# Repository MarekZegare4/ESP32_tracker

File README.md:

## Antenna tracker based on ESP32 microcontroller

This project focuses on the development of an antenna tracker with some ground station functionalities. Developed in platformio with Arduino framework. Based on [mLRS](https://github.com/olliw42/mLRS) project for MAVLink telemetry data.

### Contents of the repository
- `src` - source code of the project
- `schematic` - schematics and PCB design files
- `matlab_scripts` - magnetometer calibration routine

### Current features
- Tracking based on built-in GNSS receiver data and telemetry data from UAV
- 360° continuous rotation in vertical axis
- WiFi/BT/USB telemetry bridge
- Implemented magnetometer with calibration routine
### To be implemented
- GUI for configuration and monitoring on built-in display
- IMU pan and tilt stabilization
-
-
- More telemetry protocols

---

## Current PCB design

## Current mechanical design

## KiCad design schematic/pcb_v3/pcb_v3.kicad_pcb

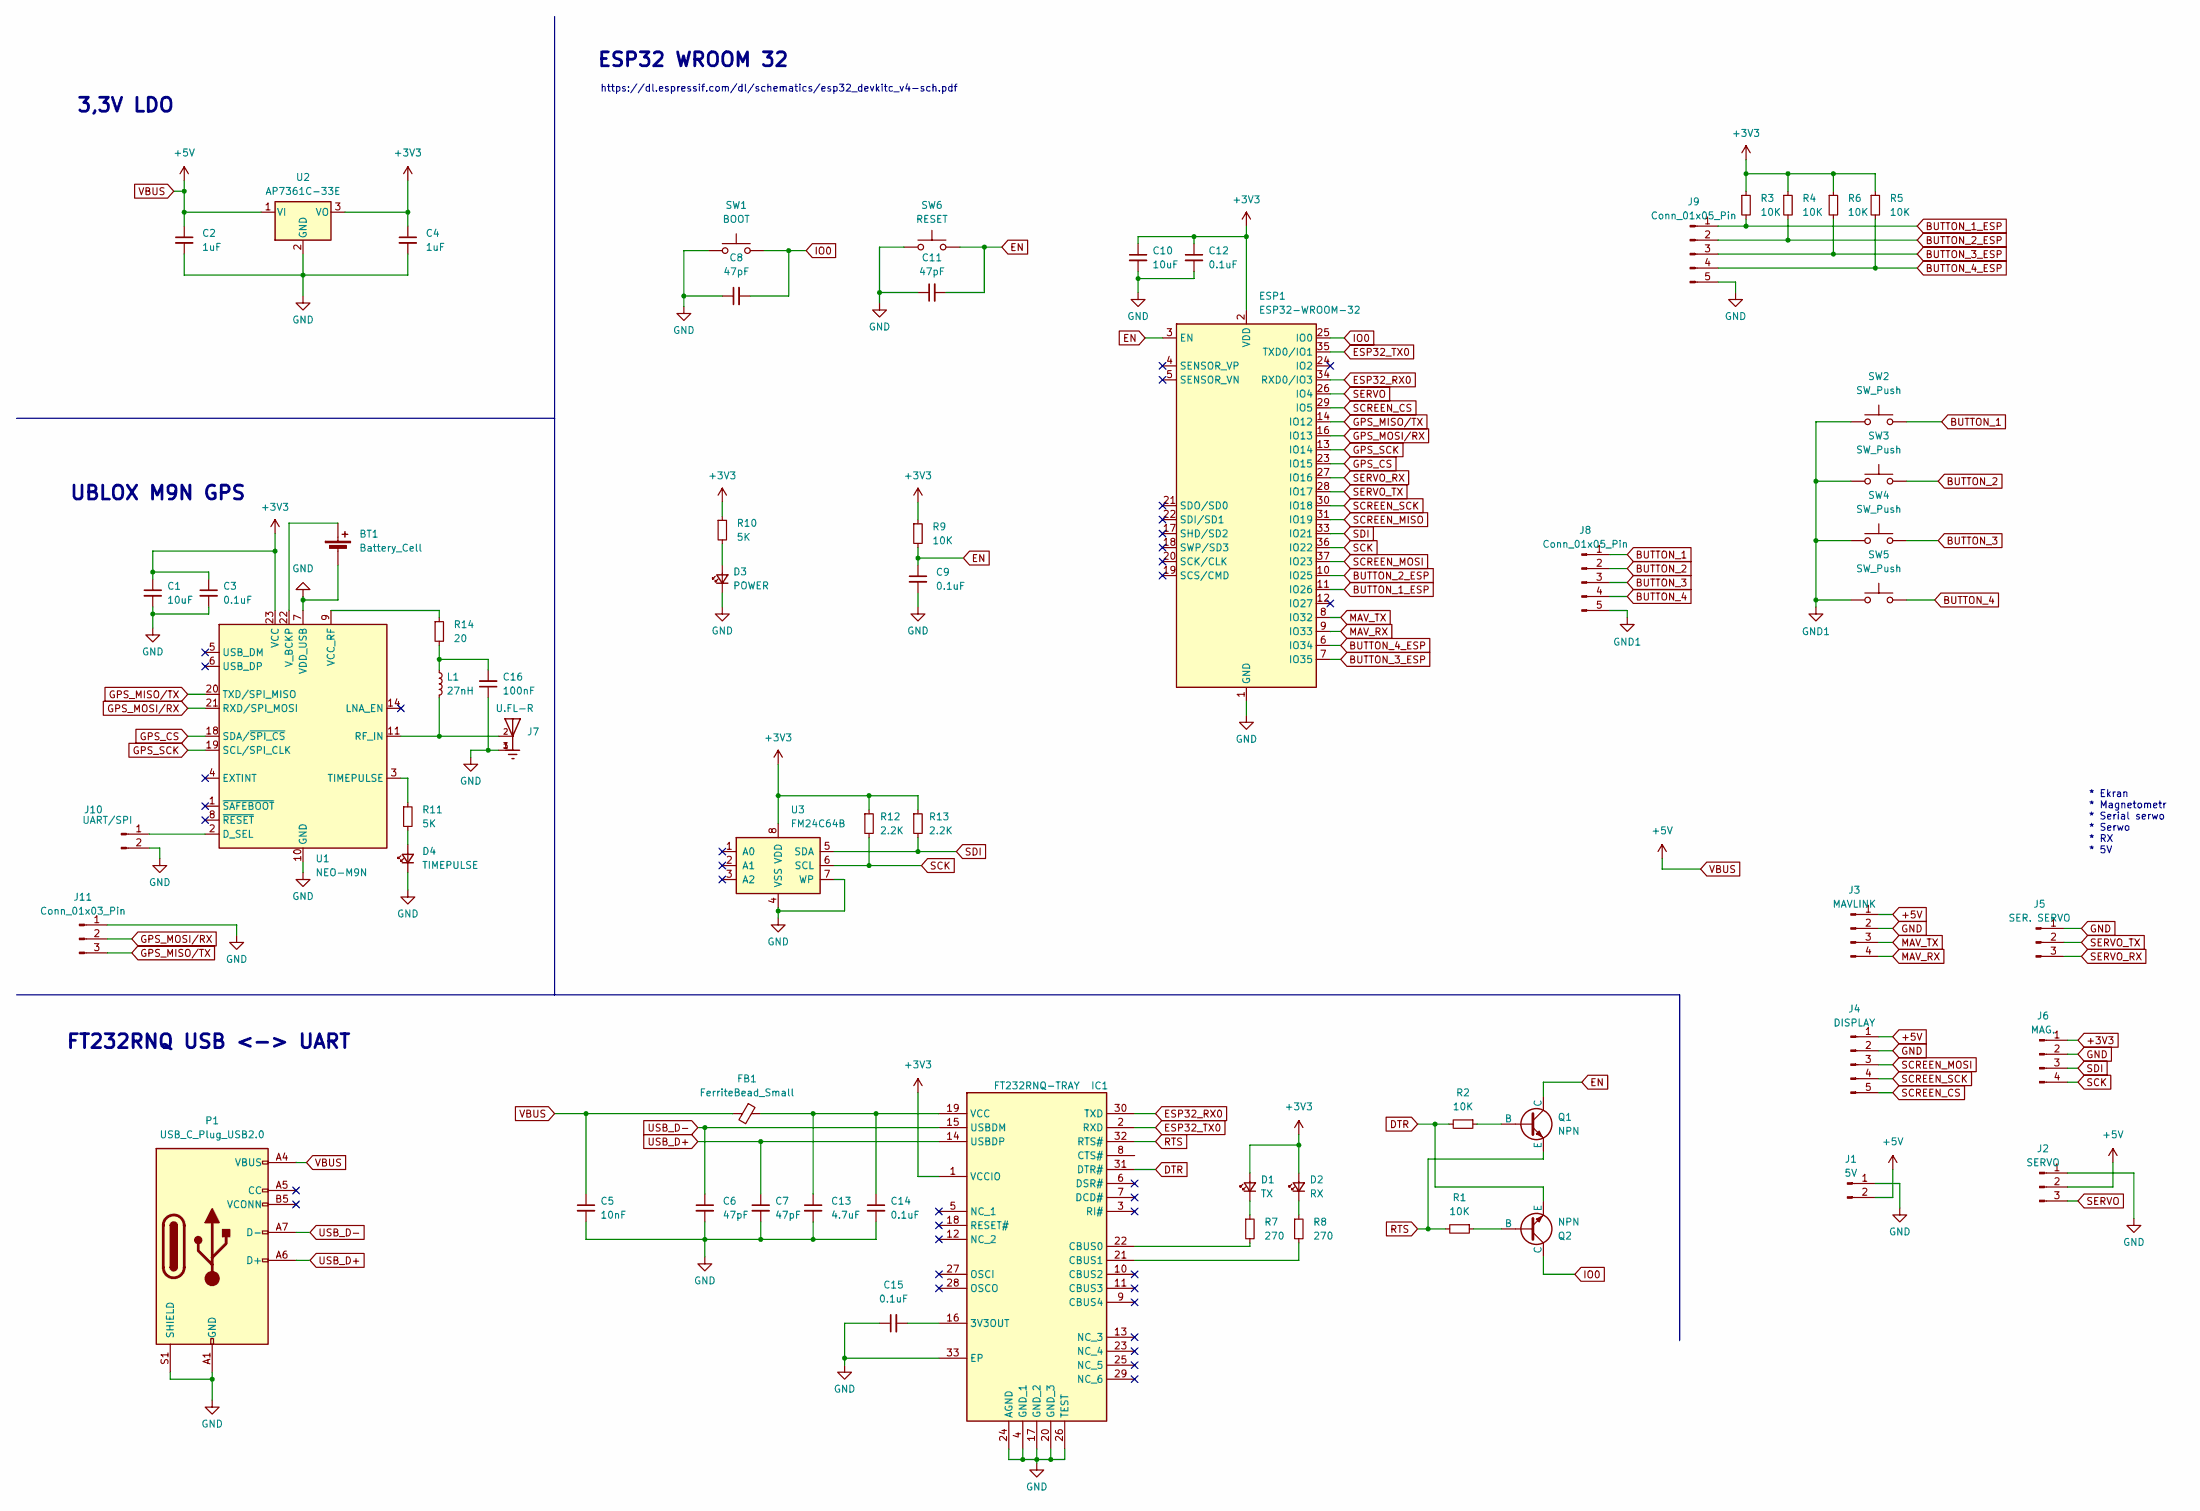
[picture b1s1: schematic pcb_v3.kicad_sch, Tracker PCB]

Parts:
BT1: Battery_Cell; BatteryHolder_Keystone_1060_1x2032
C1, C10: 10uF; C_0805_2012Metric
C2, C4: 1uF; C_0805_2012Metric
C3, C9, C12, C14, C15: 0.1uF; C_0805_2012Metric
C5: 10nF; C_0805_2012Metric
C6, C7, C8, C11: 47pF; C_0805_2012Metric
C13: 4.7uF; C_0805_2012Metric
C16: 100nF; C_0805_2012Metric
D1: TX; LED_0805_2012Metric
D2: RX; LED_0805_2012Metric
D3: POWER; LED_0805_2012Metric
D4: TIMEPULSE; LED_0805_2012Metric
ESP1: ESP32-WROOM-32; ESP32-WROOM-32UE
FB1: FerriteBead_Small; L_0805_2012Metric
IC1: FT232RNQ-TRAY; QFN50P500X500X90-33N-D; Mouser Part Number 895-FT232RNQ-TRAY
J1: 5V; PinHeader_1x02_P2.54mm_Vertical
J2: SERVO; PinHeader_1x03_P2.54mm_Vertical
J3: MAVLINK; JST_GH_BM04B-GHS-TBT_1x04-1MP_P1.25mm_Vertical
J4: DISPLAY; JST_GH_BM05B-GHS-TBT_1x05-1MP_P1.25mm_Vertical
J5: SER. SERVO; JST_GH_BM03B-GHS-TBT_1x03-1MP_P1.25mm_Vertical
J6: MAG.; JST_GH_BM04B-GHS-TBT_1x04-1MP_P1.25mm_Vertical
J7: U.FL-R; HRS_U.FL-R-SMT-1(10)
J8: Conn_01x05_Pin; PinHeader_1x05_P1.27mm_Vertical_SMD_Pin1Left
J9: Conn_01x05_Pin; JST_GH_BM05B-GHS-TBT_1x05-1MP_P1.25mm_Vertical
J10: UART/SPI; PinHeader_1x02_P2.54mm_Vertical
J11: Conn_01x03_Pin; PinHeader_1x03_P2.54mm_Vertical
L1: 27nH; L_0805_2012Metric
P1: USB_C_Plug_USB2.0; USB_C_Receptacle_HRO_TYPE-C-31-M-12
Q1, Q2: NPN; TSOT-23
R1, R2, R3, R4, R5, R6, R9: 10K; R_0805_2012Metric
R7, R8: 270; R_0805_2012Metric
R10, R11: 5K; R_0805_2012Metric
R12, R13: 2.2K; R_0805_2012Metric
R14: 20; R_0805_2012Metric
SW1: BOOT; SW_SPST_B3U-1000P
SW2, SW3, SW4, SW5: SW_Push; SW_SPST_B3SL-1002P
SW6: RESET; SW_SPST_B3U-1000P
U1: NEO-M9N; ublox_NEO
U2: AP7361C-33E; SOT-223-3_TabPin2
U3: FM24C64B; SON95P400X450X80-9N

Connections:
+3V3: C1.1, C3.1, C4.1, C10.1, C12.1, D1.2 (A), D2.2 (A), ESP1.2 (VDD), IC1.1 (VCCIO), J6.1, R3.1, R4.1, R5.1, R6.1, R9.1, R10.1, R12.1, R13.1, U1.23 (VCC), U2.3 (VO), U3.8 (VDD)
+5V: C2.1, C5.1, FB1.2, J1.2, J2.2, J3.1, J4.1, P1.A4 (VBUS), P1.A9 (VBUS), P1.B4 (VBUS), P1.B9 (VBUS), U2.1 (VI)
BUTTON_1: J8.1, SW2.2
BUTTON_1_ESP: ESP1.11 (IO26), J9.1, R3.2
BUTTON_2: J8.2, SW3.2
BUTTON_2_ESP: ESP1.10 (IO25), J9.2, R4.2
BUTTON_3: J8.3, SW4.2
BUTTON_3_ESP: ESP1.7 (IO35), J9.3, R6.2
BUTTON_4: J8.4, SW5.2
BUTTON_4_ESP: ESP1.6 (IO34), J9.4, R5.2
DTR: IC1.31 (DTR#), Q2.3 (E), R2.2
EN: C9.1, C11.2, ESP1.3 (EN), Q1.1 (C), R9.2, SW6.2
ESP32_RX0: ESP1.34 (RXD0/IO3), IC1.30 (TXD)
ESP32_TX0: ESP1.35 (TXD0/IO1), IC1.2 (RXD)
GND: BT1.2 (-), C1.2, C2.2, C3.2, C4.2, C5.2, C6.2, C7.2, C8.1, C9.2, C10.2, C11.1, C12.2, C13.2, C14.2, C15.1, C16.1, D3.1 (K), D4.1 (K), ESP1.1 (GND), ESP1.15 (GND), ESP1.38 (GND), ESP1.39 (GND), IC1.4 (GND_1), IC1.17 (GND_2), IC1.20 (GND_3), IC1.24 (AGND), IC1.26 (TEST), IC1.33 (EP), J1.1, J2.1, J3.2, J4.2, J5.1, J6.2, J7.1, J7.3, J9.5, J10.2, J11.1, P1.A1 (GND), P1.A12 (GND), P1.B1 (GND), P1.B12 (GND), P1.S1 (SHIELD), SW1.1, SW6.1, U1.7 (VDD_USB), U1.10 (GND), U1.12 (GND), U1.13 (GND), U1.24 (GND), U2.2 (GND), U3.4 (VSS), U3.7 (WP)
GND1: J8.5, SW2.1, SW3.1, SW4.1, SW5.1
GPS_CS: ESP1.23 (IO15), U1.18 (SDA/~SPI_CS)
GPS_MISO/TX: ESP1.14 (IO12), J11.3, U1.20 (TXD/SPI_MISO)
GPS_MOSI/RX: ESP1.16 (IO13), J11.2, U1.21 (RXD/SPI_MOSI)
GPS_SCK: ESP1.13 (IO14), U1.19 (SCL/SPI_CLK)
IO0: C8.2, ESP1.25 (IO0), Q2.1 (C), SW1.2
MAV_RX: ESP1.9 (IO33), J3.4
MAV_TX: ESP1.8 (IO32), J3.3
unnamed: BT1.1 (+), U1.22 (V_BCKP)
unnamed: C16.2, L1.1, R14.2
unnamed: D1.1 (K), R7.1
unnamed: D2.1 (K), R8.1
unnamed: D3.2 (A), R10.2
unnamed: D4.2 (A), R11.2
unnamed: C15.2, IC1.16 (3V3OUT)
unnamed: IC1.22 (CBUS0), R7.2
unnamed: IC1.21 (CBUS1), R8.2
unnamed: C13.1, C14.1, FB1.1, IC1.19 (VCC)
unnamed: J10.1, U1.2 (D_SEL)
unnamed: Q1.2 (B), R2.1
unnamed: Q2.2 (B), R1.1
unnamed: J7.2, L1.2, U1.11 (RF_IN)
unnamed: R11.1, U1.3 (TIMEPULSE)
unnamed: R14.1, U1.9 (VCC_RF)
RTS: IC1.32 (RTS#), Q1.3 (E), R1.2
SCK: ESP1.36 (IO22), J6.4, R12.2, U3.6 (SCL)
SCREEN_CS: ESP1.29 (IO5), J4.5
SCREEN_MISO: ESP1.31 (IO19)
SCREEN_MOSI: ESP1.37 (IO23), J4.3
SCREEN_SCK: ESP1.30 (IO18), J4.4
SDI: ESP1.33 (IO21), J6.3, R13.2, U3.5 (SDA)
SERVO: ESP1.26 (IO4), J2.3
SERVO_RX: ESP1.27 (IO16), J5.3
SERVO_TX: ESP1.28 (IO17), J5.2
USB_D+: C7.1, IC1.14 (USBDP), P1.A6 (D+)
USB_D-: C6.1, IC1.15 (USBDM), P1.A7 (D-)

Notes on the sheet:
* Ekran * Magnetometr * Serial serwo * Serwo * RX * 5V
FT232RNQ USB <-> UART
https://dl.espressif.com/dl/schematics/esp32_devkitc_v4-sch.pdf
3,3V LDO
ESP32 WROOM 32
UBLOX M9N GPS

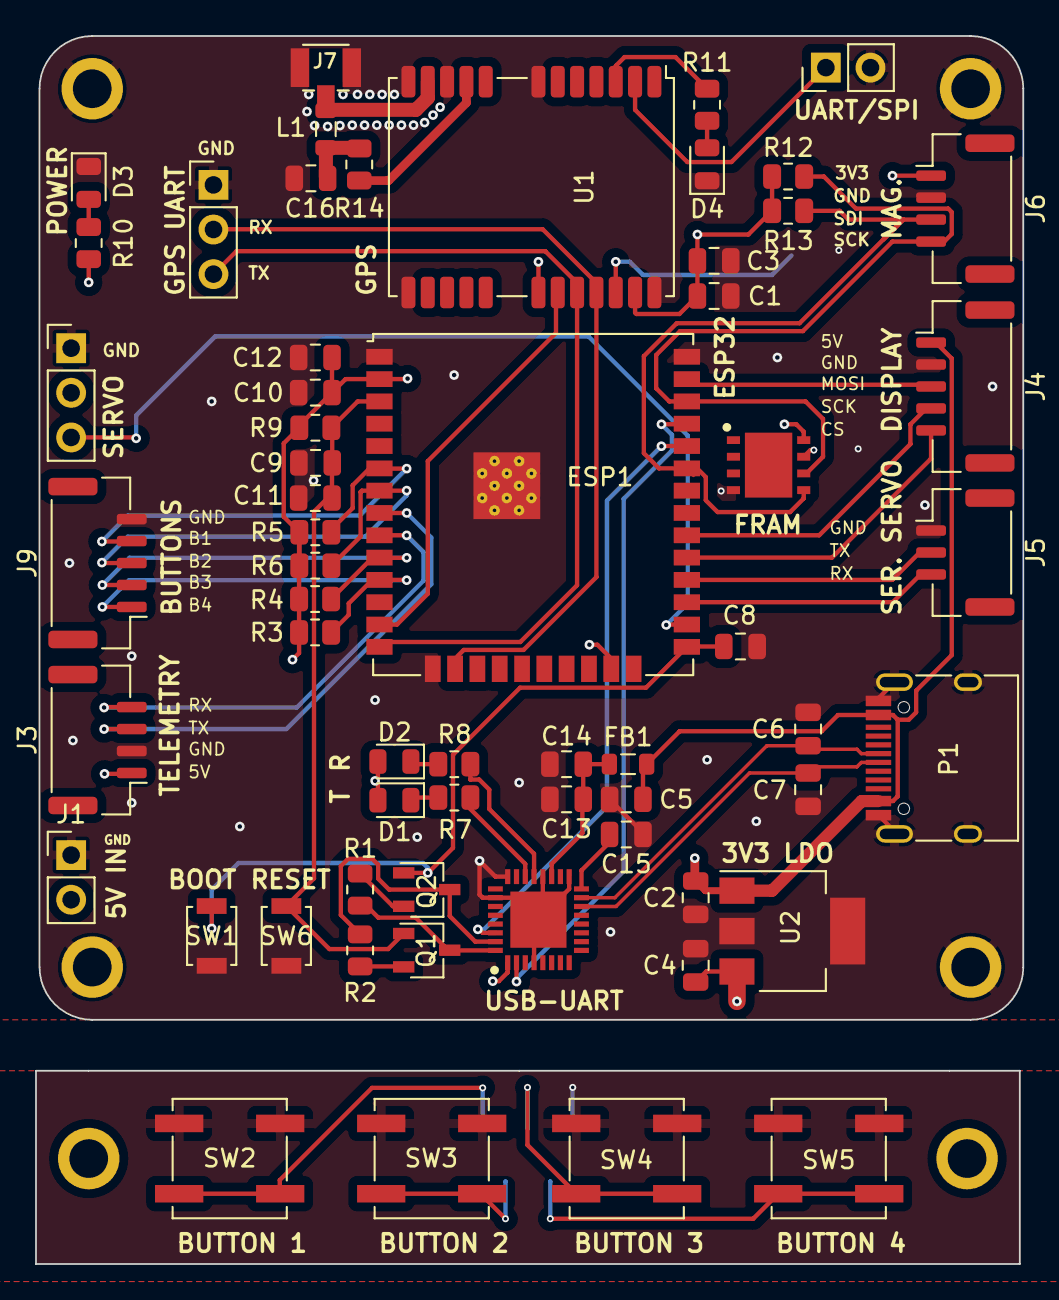
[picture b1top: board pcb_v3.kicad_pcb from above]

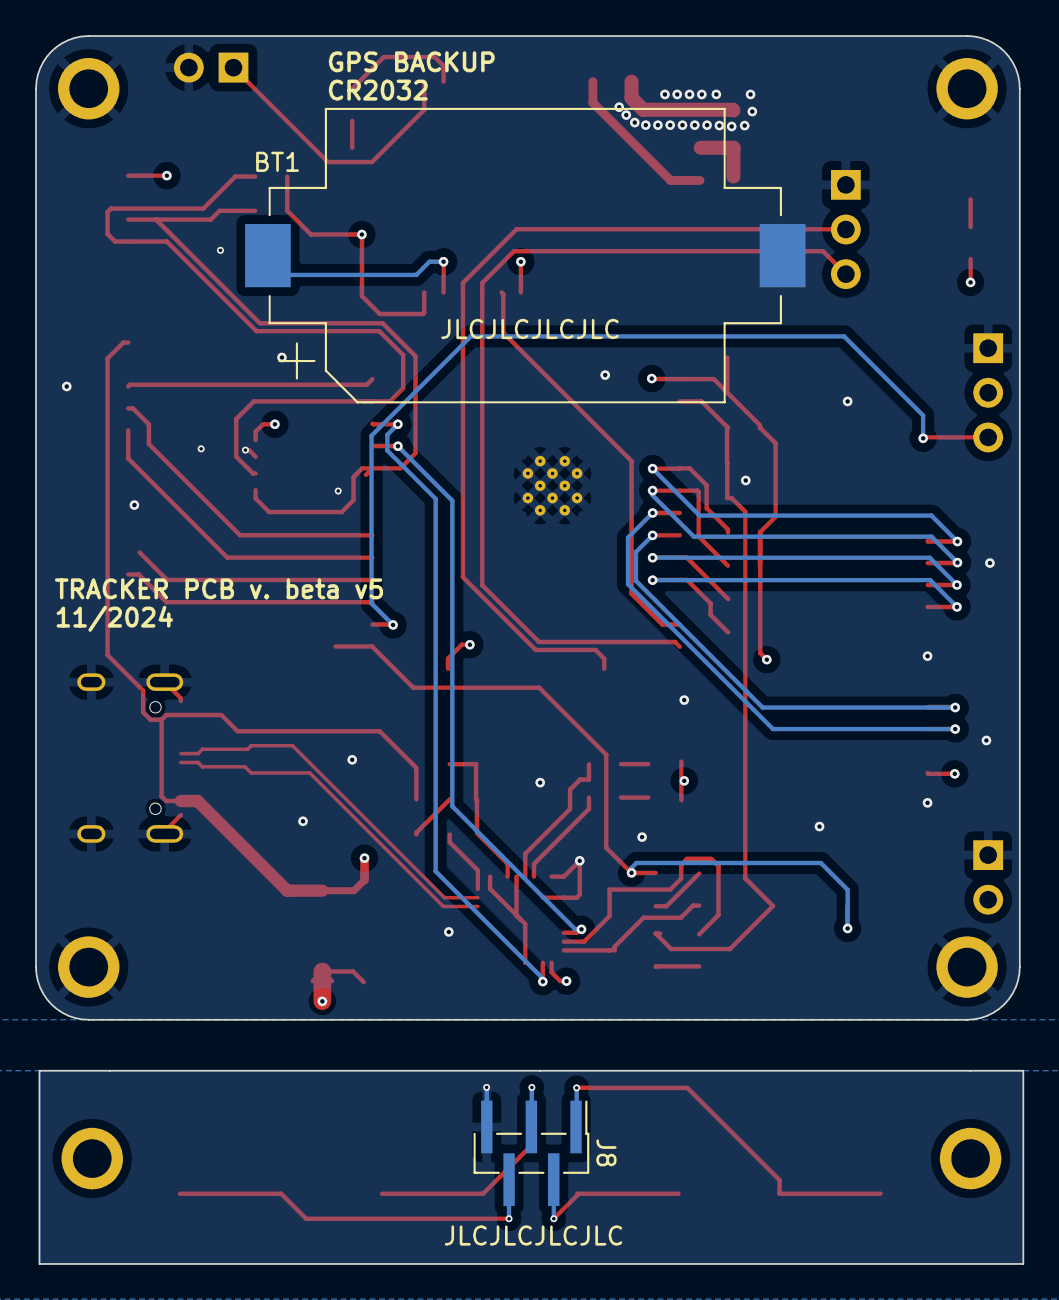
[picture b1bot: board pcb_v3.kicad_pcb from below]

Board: 4 copper layers, 56.2 x 69.9 mm, 62 parts (2 on the bottom side), 50 nets.

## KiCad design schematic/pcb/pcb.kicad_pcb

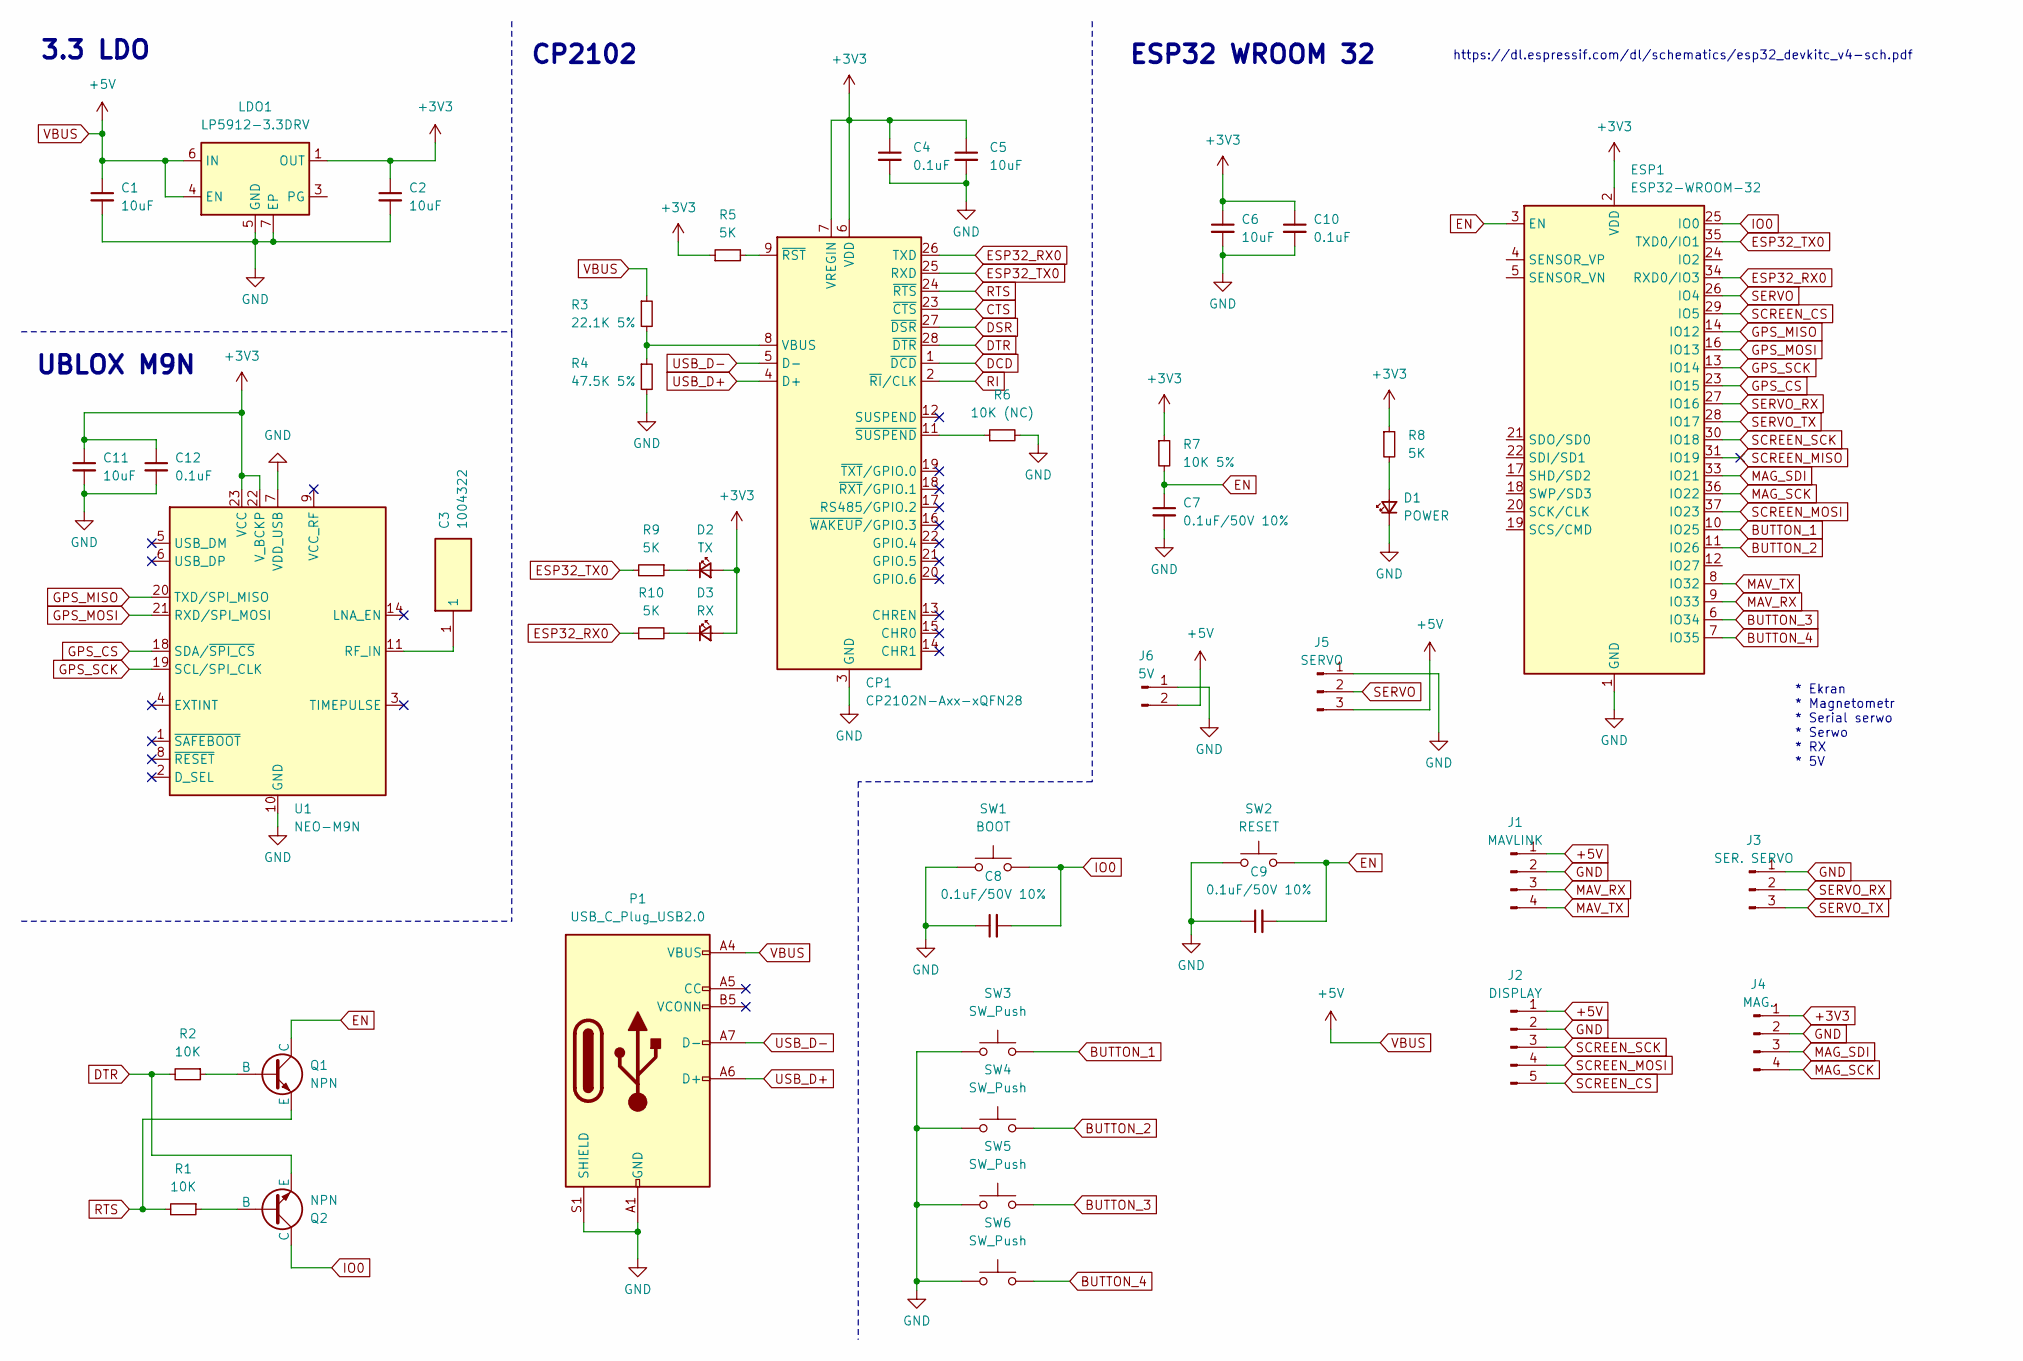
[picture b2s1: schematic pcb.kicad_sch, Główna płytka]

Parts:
C1, C2, C5, C6, C11: 10uF; C_0805_2012Metric
C3: 1004322; GPS_ANTENNA; Mouser Part Number 581-1004322
C4, C10, C12: 0.1uF; C_0805_2012Metric
C7, C8, C9: 0.1uF/50V 10%; C_0805_2012Metric
CP1: CP2102N-Axx-xQFN28; QFN-28-1EP_5x5mm_P0.5mm_EP3.35x3.35mm
D1: POWER; LED_0805_2012Metric
D2: TX; LED_0805_2012Metric
D3: RX; LED_0805_2012Metric
ESP1: ESP32-WROOM-32
J1: MAVLINK; JST_GH_BM04B-GHS-TBT_1x04-1MP_P1.25mm_Vertical
J2: DISPLAY; JST_GH_BM05B-GHS-TBT_1x05-1MP_P1.25mm_Vertical
J3: SER. SERVO; JST_GH_BM03B-GHS-TBT_1x03-1MP_P1.25mm_Vertical
J4: MAG.; JST_GH_BM04B-GHS-TBT_1x04-1MP_P1.25mm_Vertical
J5: SERVO; PinHeader_1x03_P2.54mm_Vertical
J6: 5V; PinHeader_1x02_P2.54mm_Vertical
LDO1: LP5912-3.3DRV; WSON-6-1EP_2x2mm_P0.65mm_EP1x1.6mm_ThermalVias
P1: USB_C_Plug_USB2.0; USB_C_Receptacle_HRO_TYPE-C-31-M-12
Q1, Q2: NPN; TSOT-23
R1, R2: 10K; R_0805_2012Metric
R3: 22.1K 5%; R_0805_2012Metric
R4: 47.5K 5%; R_0805_2012Metric
R5, R8, R9, R10: 5K; R_0805_2012Metric
R6: 10K (NC); R_0805_2012Metric
R7: 10K 5%; R_0805_2012Metric
SW1: BOOT; SW_SPST_B3U-1000P
SW2: RESET; SW_SPST_B3U-1000P
SW3, SW4, SW5, SW6: SW_Push; SW_SPST_B3SL-1002P
U1: NEO-M9N; ublox_NEO

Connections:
+3V3: C2.1, C4.1, C5.1, C6.1, C10.1, C11.1, C12.1, CP1.6 (VDD), CP1.7 (VREGIN), D2.2 (A), D3.2 (A), ESP1.2 (VDD), J4.1, LDO1.1 (OUT), R5.1, R7.1, R8.1, U1.22 (V_BCKP), U1.23 (VCC)
+5V: C1.1, J1.1, J2.1, J5.3, J6.2, LDO1.4 (EN), LDO1.6 (IN), P1.A4 (VBUS), P1.A9 (VBUS), P1.B4 (VBUS), P1.B9 (VBUS), R3.1
BUTTON_1: ESP1.10 (IO25), SW3.2
BUTTON_2: ESP1.11 (IO26), SW4.2
BUTTON_3: ESP1.6 (IO34), SW5.2
BUTTON_4: ESP1.7 (IO35), SW6.2
CTS: CP1.23 (~CTS)
DCD: CP1.1 (~DCD)
DSR: CP1.27 (~DSR)
DTR: CP1.28 (~DTR), Q2.3 (E), R2.2
EN: C7.1, C9.2, ESP1.3 (EN), Q1.1 (C), R7.2, SW2.2
ESP32_RX0: CP1.26 (TXD), ESP1.34 (RXD0/IO3), R10.1
ESP32_TX0: CP1.25 (RXD), ESP1.35 (TXD0/IO1), R9.2
GND: C1.2, C2.2, C4.2, C5.2, C6.2, C7.2, C8.1, C9.1, C10.2, C11.2, C12.2, CP1.3 (GND), CP1.29 (GND), D1.1 (K), ESP1.1 (GND), ESP1.15 (GND), ESP1.38 (GND), ESP1.39 (GND), J1.2, J2.2, J3.1, J4.2, J5.1, J6.1, LDO1.5 (GND), LDO1.7 (EP), P1.A1 (GND), P1.A12 (GND), P1.B1 (GND), P1.B12 (GND), P1.S1 (SHIELD), R4.2, R6.2, SW1.1, SW2.1, SW3.1, SW4.1, SW5.1, SW6.1, U1.7 (VDD_USB), U1.10 (GND), U1.12 (GND), U1.13 (GND), U1.24 (GND)
GPS_CS: ESP1.23 (IO15), U1.18 (SDA/~SPI_CS)
GPS_MISO: ESP1.14 (IO12), U1.20 (TXD/SPI_MISO)
GPS_MOSI: ESP1.16 (IO13), U1.21 (RXD/SPI_MOSI)
GPS_SCK: ESP1.13 (IO14), U1.19 (SCL/SPI_CLK)
IO0: C8.2, ESP1.25 (IO0), Q2.1 (C), SW1.2
MAG_SCK: ESP1.36 (IO22), J4.4
MAG_SDI: ESP1.33 (IO21), J4.3
MAV_RX: ESP1.9 (IO33), J1.3
MAV_TX: ESP1.8 (IO32), J1.4
unnamed: CP1.8 (VBUS), R3.2, R4.1
unnamed: CP1.9 (~RST), R5.2
unnamed: CP1.11 (~SUSPEND), R6.1
unnamed: D1.2 (A), R8.2
unnamed: D2.1 (K), R9.1
unnamed: D3.1 (K), R10.2
unnamed: Q1.2 (B), R2.1
unnamed: Q2.2 (B), R1.1
unnamed: C3.1, U1.11 (RF_IN)
RI: CP1.2 (~RI/CLK)
RTS: CP1.24 (~RTS), Q1.3 (E), R1.2
SCREEN_CS: ESP1.29 (IO5), J2.5
SCREEN_MISO: ESP1.31 (IO19)
SCREEN_MOSI: ESP1.37 (IO23), J2.4
SCREEN_SCK: ESP1.30 (IO18), J2.3
SERVO: ESP1.26 (IO4), J5.2
SERVO_RX: ESP1.27 (IO16), J3.2
SERVO_TX: ESP1.28 (IO17), J3.3
USB_D+: CP1.4 (D+), P1.A6 (D+)
USB_D-: CP1.5 (D-), P1.A7 (D-)

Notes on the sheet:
CP2102
* Ekran * Magnetometr * Serial serwo * Serwo * RX * 5V
https://dl.espressif.com/dl/schematics/esp32_devkitc_v4-sch.pdf
UBLOX M9N
ESP32 WROOM 32
3.3 LDO

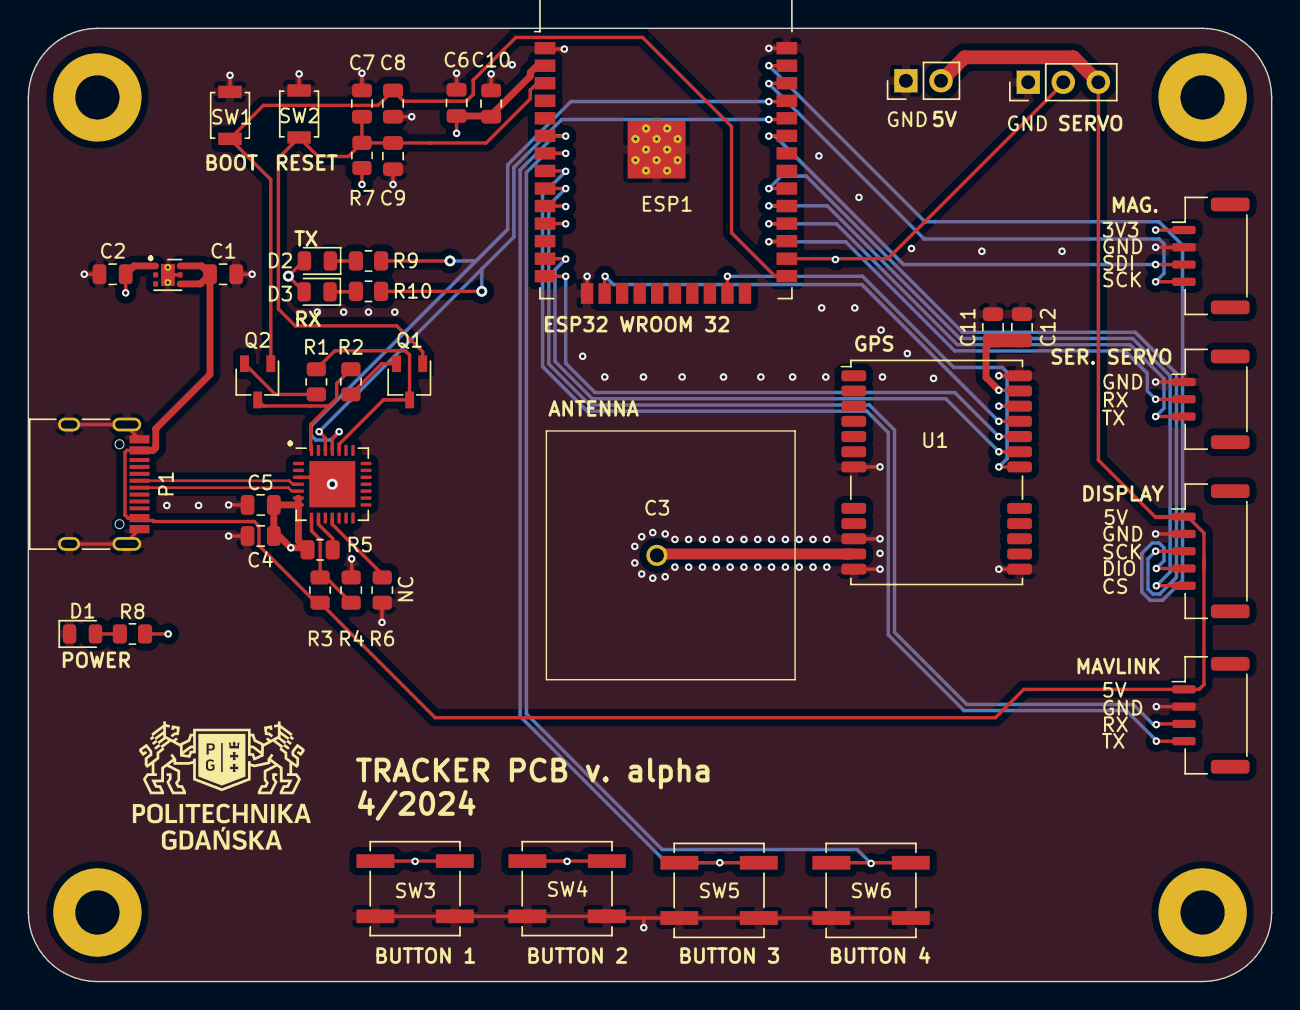
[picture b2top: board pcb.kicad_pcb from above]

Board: 4 copper layers, 90.0 x 69.0 mm, 44 parts (0 on the bottom side), 38 nets.

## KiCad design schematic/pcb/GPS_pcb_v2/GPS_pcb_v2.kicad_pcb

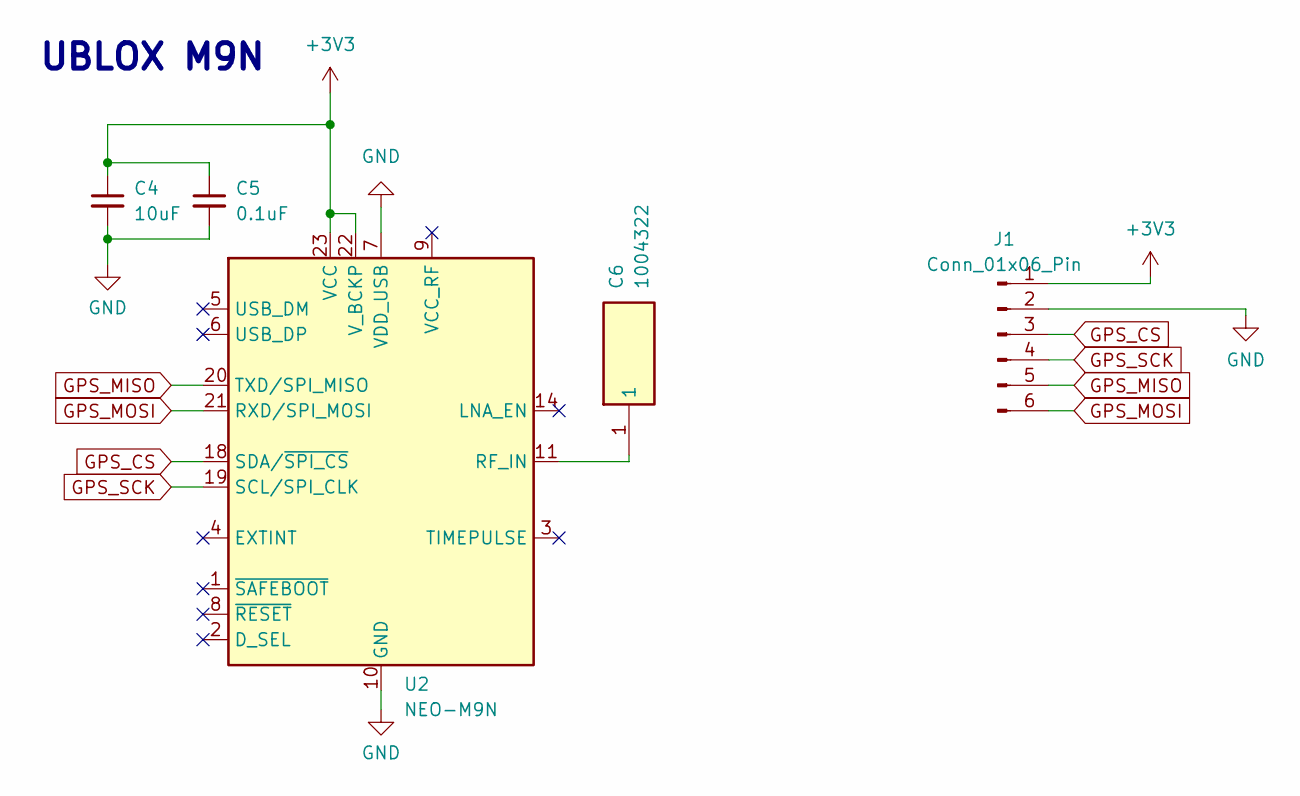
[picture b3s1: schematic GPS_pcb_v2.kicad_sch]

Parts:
C4: 10uF; C_0805_2012Metric
C5: 0.1uF; C_0805_2012Metric
C6: 1004322; GPS_ANTENNA; Mouser Part Number 581-1004322
J1: Conn_01x06_Pin; JST_GH_BM06B-GHS-TBT_1x06-1MP_P1.25mm_Vertical
U2: NEO-M9N; ublox_NEO

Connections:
+3V3: C4.1, C5.1, J1.1, U2.22 (V_BCKP), U2.23 (VCC)
GND: C4.2, C5.2, J1.2, U2.7 (VDD_USB), U2.10 (GND), U2.12 (GND), U2.13 (GND), U2.24 (GND)
GPS_CS: J1.3, U2.18 (SDA/~SPI_CS)
GPS_MISO: J1.5, U2.20 (TXD/SPI_MISO)
GPS_MOSI: J1.6, U2.21 (RXD/SPI_MOSI)
GPS_SCK: J1.4, U2.19 (SCL/SPI_CLK)
unnamed: C6.1, U2.11 (RF_IN)

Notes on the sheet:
UBLOX M9N

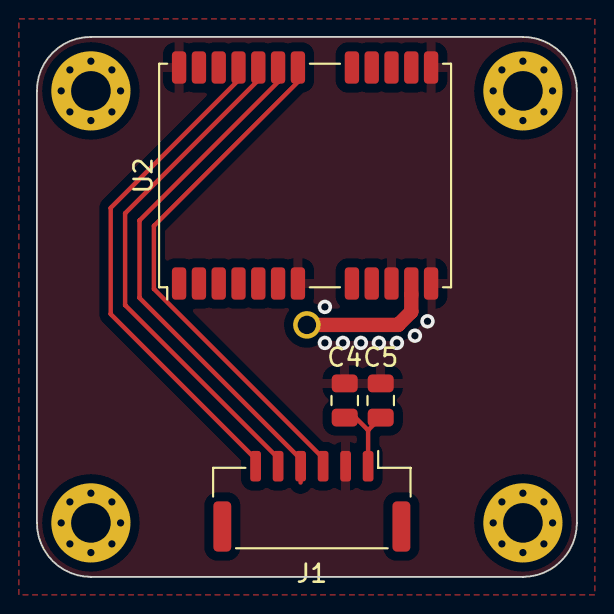
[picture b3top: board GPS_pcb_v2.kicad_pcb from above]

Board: 2 copper layers, 30.0 x 30.0 mm, 5 parts (1 on the bottom side), 7 nets.

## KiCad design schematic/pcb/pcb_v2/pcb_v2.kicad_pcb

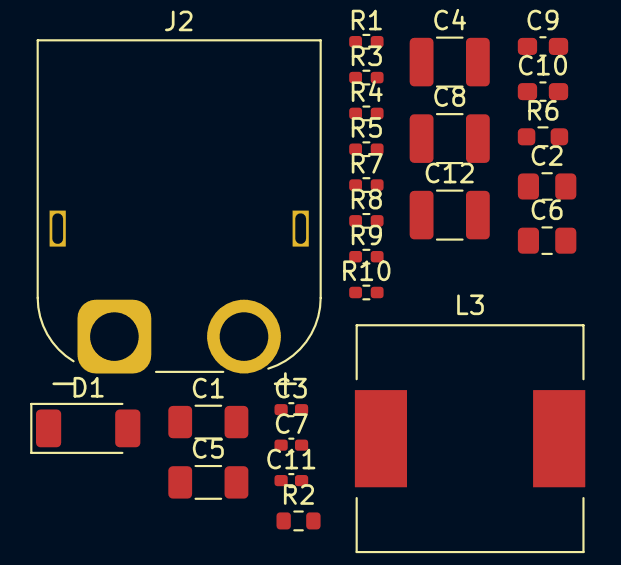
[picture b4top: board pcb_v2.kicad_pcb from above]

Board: 2 copper layers, 25 parts (0 on the bottom side), 10 nets, no tracks yet.

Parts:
C1, C5: 4.7uF; C_1206_3216Metric_Pad1.33x1.80mm_HandSolder
C2, C6: 100nF; C_0805_2012Metric_Pad1.18x1.45mm_HandSolder
C3, C7, C11: 100nF; C_0402_1005Metric_Pad0.74x0.62mm_HandSolder
C4: 100uF; C_1210_3225Metric_Pad1.33x2.70mm_HandSolder
C8, C12: 47uF; C_1210_3225Metric_Pad1.33x2.70mm_HandSolder
C9: 4.7uF; C_0603_1608Metric_Pad1.08x0.95mm_HandSolder
C10: 100nF; C_0603_1608Metric_Pad1.08x0.95mm_HandSolder
D1: D_Small; D_SOD-128
J2: XT60PW-M; AMASS_XT60PW-M_1x02_P7.20mm_Horizontal
L3: 15uH; L_12x12mm_H8mm
R1: 18.7k; R_0402_1005Metric_Pad0.72x0.64mm_HandSolder
R2: 100k; R_0603_1608Metric
R3, R7: 100k; R_0402_1005Metric_Pad0.72x0.64mm_HandSolder
R4: 32k; R_0402_1005Metric_Pad0.72x0.64mm_HandSolder
R5: 13.3k; R_0402_1005Metric_Pad0.72x0.64mm_HandSolder
R6: 100k; R_0603_1608Metric_Pad0.98x0.95mm_HandSolder
R8: 19.1k; R_0402_1005Metric_Pad0.72x0.64mm_HandSolder
R9: 422k; R_0402_1005Metric_Pad0.72x0.64mm_HandSolder
R10: 22.1k; R_0402_1005Metric_Pad0.72x0.64mm_HandSolder

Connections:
3V3_FB: R3.2, R4.1
5V_FB: R7.2, R8.1
12V_SW: C11.2, L3.1
+3V3: C4.1, R2.2, R3.1
+5V: C8.1, R6.2, R7.1
+12V: C12.2, L3.2, R9.1
+24V: C1.1, C2.1, C5.1, C6.1, C9.1, C10.1, D1.1 (K)
/FB_12V: R9.2, R10.1
GND: C1.2, C2.2, C4.2, C5.2, C6.2, C8.2, C9.2, C10.2, C12.1, J2.1, R1.2, R4.2, R5.2, R8.2, R10.2
unnamed: D1.2 (A), J2.2

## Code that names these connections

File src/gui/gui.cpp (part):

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#define WHITE 1
#define FREQ_2MHZ 2000000
#define FPS 30
#define BUTTON_1_PIN 26
#define BUTTON_2_PIN 25
#define BUTTON_3_PIN 35
#define BUTTON_4_PIN 34

// Useful links:
// https://javl.github.io/image2cpp/
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 */
void guiInitialize()
{
	pinMode(BUTTON_1_PIN, INPUT);
	pinMode(BUTTON_2_PIN, INPUT);
	pinMode(BUTTON_3_PIN, INPUT);
	pinMode(BUTTON_4_PIN, INPUT);
	attachInterrupt(digitalPinToInterrupt(BUTTON_1_PIN), button_1ISR, FALLING);
	attachInterrupt(digitalPinToInterrupt(BUTTON_2_PIN), button_2ISR, FALLING);
	attachInterrupt(digitalPinToInterrupt(BUTTON_3_PIN), button_3ISR, FALLING);
	attachInterrupt(digitalPinToInterrupt(BUTTON_4_PIN), button_4ISR, FALLING);
	display.begin();
	display.clearDisplay();
}
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
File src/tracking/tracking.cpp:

#include <Arduino.h>
#include <SCServo.h>
#include <Wire.h>
#include <SPI.h>
#include <Adafruit_LIS3MDL.h>
#include <Adafruit_LSM6DS3TRC.h>
#include <Adafruit_Sensor.h>
#include <ESP32Servo.h>
#include <SparkFun_u-blox_GNSS_v3.h>
#include <WMM_Tinier.h>
#include <SensorFusion.h>
#include "gui/gui.h"
#include "mavlink/mav.h"
#include "tracking.h"
#include "tracking/geoTransform/geoTransform.h"
#include "imu_calibration/imu_calibration.h"
#include "kalman_filter/kalman.h"
// https://www.waveshare.com/wiki/ST3020_Servo#Overview

#define SERVO_RX 16
#define SERVO_TX 17
#define SERVO_TILT_PIN 4
#define myCS 15              // Define the GPIO pin number for the SPI Chip Select. Change this if required
#define myClockSpeed 1000000 // Define what SPI clock speed to use. Change this if required

Servo servo;
// Serial Servo ST3020
SMS_STS st;
// Magnetometer
Adafruit_LIS3MDL lis3mdl;
// Accelerometer and Gyroscope
Adafruit_LSM6DS3TRC lsm6ds3trc;
// GNSS
SFE_UBLOX_GNSS_SPI myGNSS; // SFE_UBLOX_GNSS_SPI uses SPI. For I2C or Serial, see Example1 and Example2
SPIClass spiPort(HSPI);

WMM_Tinier declination;
TrackerDataGPS gpsData;
AngleValues sDistAziElev;
float sCompassDegree;
Wgs84Coord uavCoord;
Wgs84Coord trackerCoord;

// Sensor fusion
SF fusion;
float mx, my, mz, ax, ay, az, gx, gy, gz;
float pitch, roll, yaw;
float deltat;
float heading;

CalibratedIMUData mag_data;
CalibratedIMUData accel_data;

bool ready_to_track = false;

/*
@brief Corrects the angle to work in the current configuration
@param angle: wanted angle
*/
int servoAngle(int angle)
{
  return map(angle, 0, 90, 14, 170);
}

void trackingInitialize()
{
  Serial1.begin(1000000, SERIAL_8N1, SERVO_RX, SERVO_TX);
  declination.begin();
  st.pSerial = &Serial1;
  // st.CalibrationOfs(1);
  st.WritePosEx(1, 0, 1000, 100);
  ESP32PWM::allocateTimer(0);
  servo.setPeriodHertz(50);                 // Standard 50hz servo
  servo.attach(SERVO_TILT_PIN, 1000, 2000); // attaches the servo on pin 4 to the servo object
  servo.write(servoAngle(0));
  lis3mdl.begin_I2C();
  lis3mdl.setRange(LIS3MDL_RANGE_4_GAUSS);
  lis3mdl.setDataRate(LIS3MDL_DATARATE_80_HZ);
  lis3mdl.setPerformanceMode(LIS3MDL_HIGHMODE);
  lis3mdl.setOperationMode(LIS3MDL_CONTINUOUSMODE);
  lsm6ds3trc.begin_I2C();
  lsm6ds3trc.setGyroDataRate(LSM6DS_RATE_104_HZ);
  lsm6ds3trc.setAccelDataRate(LSM6DS_RATE_104_HZ);
  while (myGNSS.begin(spiPort, myCS, myClockSpeed) == false) // Connect to the u-blox module using the port, chip select pin and speed defined above
  {
    delay(1000);
  }
  myGNSS.setSPIOutput(COM_TYPE_UBX); // Set the SPI port to output UBX only (turn off NMEA noise)
  myGNSS.setNavigationFrequency(5);  // Set the update rate to 5Hz
}

void sendRawMagData()
{
  sensors_event_t mag;
  lis3mdl.getEvent(&mag);
  Serial.print(String(mag.magnetic.x) + " " + String(mag.magnetic.y) + " " + String(mag.magnetic.z) + "\n");
}

int angleToServo(int angle)
{
  return map(angle, 0, 360, 0, 4096);
}

int servoToAngle(int servo)
{
  return map(servo, 0, 4096, 0, 360);
}

void moveServoByAngle(int angle, int speed, int acc){
  int current_angle = servoToAngle(st.ReadPos(1));
  st.WritePosEx(1, angleToServo(current_angle + angle) % 4096, speed, acc);
}

void servoDemo()
{
  st.WritePosEx(1, 0, 1000, 100);
  delay(10000);
  st.WritePosEx(1, 2048, 1000, 100);
  delay(10000);
}

int readCurrent()
{
  return st.ReadCurrent(1);
}

TrackerDataGPS getTrackerGPS()
{
  return gpsData;
}

float readHeading()
{
  return heading;
}

sensor_t sensor;
float x, y, z;
int i = 0;
bool date_flag = false;
float mag_declination = 0;

void trackingTask(void *parameters)
{
  for (;;)
  {
    // Orientation calculation
    // Update IMU readings
    sensors_event_t mag;
    sensors_event_t accel;
    sensors_event_t gyro;
    sensors_event_t temp;
    lis3mdl.getEvent(&mag);
    lsm6ds3trc.getEvent(&accel, &gyro, &temp);

    mag_data = calibratedMagData(mag.magnetic.x, mag.magnetic.y, mag.magnetic.z);
    accel_data = calibratedAccData(accel.acceleration.x, accel.acceleration.y, accel.acceleration.z);
    // mx = mag_data.x;
    // my = mag_data.y;
    // mz = mag_data.z;
    // ax = accel_data.x;
    // ay = accel_data.y;
    // az = accel_data.z;
    // gx = gyro.gyro.x;
    // gy = gyro.gyro.y;
    // gz = gyro.gyro.z;
    // deltat = fusion.deltatUpdate();
    // fusion.MadgwickUpdate(gx, gy, gz, ax, ay, az, mx, my, mz, deltat);

    // pitch = pitchKalman(fusion.getPitch());
    // roll = rollKalman(fusion.getRoll());

    // Read data from GNSS module
    gpsData.latitude = myGNSS.getLatitude();
    gpsData.longitude = myGNSS.getLongitude();
    gpsData.altitude = myGNSS.getAltitudeMSL();
    gpsData.fixType = myGNSS.getFixType();
    gpsData.satCount = myGNSS.getSIV();

    gpsData.day = myGNSS.getDay();
    gpsData.month = myGNSS.getMonth();
    gpsData.year = myGNSS.getYear();

    trackerCoord.lat = gpsData.latitude;
    trackerCoord.lon = gpsData.longitude;
    trackerCoord.alt = gpsData.altitude;

    uavCoord.lat = getUavGPS()->global_lat;
    uavCoord.lon = getUavGPS()->global_lon;
    uavCoord.alt = getUavGPS()->global_alt;

    if (gpsData.fixType >= 3 && !date_flag)
    {
      mag_declination = declination.magneticDeclination(gpsData.latitude, gpsData.longitude, myGNSS.getYear() % 100, myGNSS.getMonth(), myGNSS.getDay());
      date_flag = true;
    }
  
    // heading = convertHeading(headingKalman(tiltCompensatedHeading(mag_data.x, mag_data.y, mag_data.z, pitch, roll)), -90 + declination.magneticDeclination(gpsData.latitude, gpsData.longitude, myGNSS.getYear() % 100, myGNSS.getMonth(), myGNSS.getDay()));
    if (gpsData.fixType >= 3)
    {
      heading = convertHeading(headingKalman(atan2(mag_data.y, mag_data.x) * 180 / PI), -90 + mag_declination); 
      if(i <= 100){
        i++;
      }
      if (i >= 100 && !ready_to_track)
      {
        moveServoByAngle((int)(abs(heading - 180)) % 360, 1000, 100);
        st.CalibrationOfs(1);
        delay(2000);
        ready_to_track = true;
      }
      if (ready_to_track)
      {
        gpsData.angles = distAziElev(trackerCoord, uavCoord);
        st.WritePosEx(1, angleToServo((int)gpsData.angles.azimuth), 1000, 100);
        servo.write(servoAngle((int)gpsData.angles.elevation));
      }
    }
    else
    {
      heading = convertHeading(headingKalman(atan2(mag_data.y, mag_data.x) * 180 / PI), -90 );
      //Serial.println("______________________________");
      // Serial.println(servoToAngle(st.ReadPos(1)));
      // //Serial.println(servoToAngle(servoToAngle(st.ReadPos(1)) + heading));
      // Serial.println((int)(abs(heading - 180)) % 360);
      //Serial.println(heading);
      // Serial.println(i);
      // if(i <= 100){
      //   i++;
      // }
      // if (i >= 100 && !ready_to_track)
      // {
      //   //st.WritePosEx(1, angleToServo(servoToAngle(st.ReadPos(1)) + heading), 1000, 100);
      //   moveServoByAngle((int)(abs(heading - 180)) % 360, 1000, 100);
      //   delay(5000);
      //   st.CalibrationOfs(1);
      //   delay(1000);
      //   ready_to_track = true;
      // }
      // heading = convertHeading(headingKalman(tiltCompensatedHeading(mag_data.x, mag_data.y, mag_data.z, pitch, roll)), -90);
    }
    vTaskDelay(10 / portTICK_PERIOD_MS);
  }
}

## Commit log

2024-01-04 test
2024-01-04 task update
2024-01-10 change esp board
2024-02-21 updt
2024-02-21 -tmc
2024-02-22 mavlink
2024-02-23 dodane biblioteki
2024-02-24 display test
2024-02-29 udp + kolejka
2024-03-05 pcb #2
2024-03-06 schematic update
2024-03-08 schematic udpt
2024-03-08 ldo added
2024-03-11 boops bops
2024-03-15 poskładane w osobne pliki
2024-03-17 screen working
2024-03-17 new msgs
2024-03-18 split files, print on screen
2024-03-19 lib changes
2024-03-19 partition size update
2024-03-20 working queue, all working
2024-03-21 display changes
2024-03-22 bt working?
2024-03-22 cleanup
2024-03-22 broken display
2024-03-22 tweaks
2024-03-22 working
2024-03-24 platformio.ini update
2024-03-26 pcb updt
2024-03-26 pcb update
2024-04-02 trzymam kciuki
2024-04-03 niechaj działa
2024-04-03 włączany most
2024-04-03 small changes
2024-04-03 lets go
2024-04-03 jest dobrze
2024-04-04 naming convention cleanup
2024-04-04 more cleanup
2024-04-04 added comments
2024-04-06 add readme
2024-04-07 artificial horizon cross
2024-04-09 function names, new delays
2024-04-11 new pcb
2024-04-12 board update
2024-04-12 v. alpha pcb
2024-04-12 v. alpha pcb 2
2024-04-13 pcb v3
2024-04-13 added leds
2024-04-13 pcb final v1
2024-04-23 inventor model, geotransform coeff param
2024-05-05 gps tweaks
2024-05-05 fixes
2024-05-07 button tests
2024-05-10 pcb v beta, gui update
2024-05-11 pcb update, bluetooth bridge working
2024-06-12 pcb updates
2024-06-12 minor cleanup
2024-06-17 status screen
2024-06-17 sys text first steps
2024-07-01 tracker messages
2024-08-19 gui update
2024-09-02 work plan, lets go
2024-09-02 menu framework, readme update
2024-09-02 work tracker
2024-09-02 menu working, some upgardes
2024-09-03 more menu tweaks
2024-09-03 readme update
2024-09-04 add function descriptions
2024-09-07 work tracker update
2024-09-21 serial servo test, added library for geomagnetic declination calculation
2024-09-26 pcb bad via, tests
2024-10-02 tests, sources
2024-10-04 one less task
2024-10-10 fram, gps uart
2024-10-10 pcb cleanup
2024-10-14 task reduction progress
2024-10-16 final pcb please
2024-10-16 code minimalization and optimization
2024-10-17 bridge interface
2024-10-27 updates, geotransform formula fix
2024-11-12 magnetometer interface, cleanup
2024-11-12 acc correction matrices, calibration script
2024-11-14 kalman filtering
2024-11-23 tests
2024-11-29 correct heartbeat, misc
